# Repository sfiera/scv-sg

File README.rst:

Super Cassette Vision with Sega controllers
===========================================

.. image:: doc/pcb.png
   :alt: Adapter PCB
   :width: 400

This is an adapter board to connect early Sega controllers (SG-1000, SMS, Mega Drive) to an Epoch Super Cassette Vision console.

Schematic
---------

.. image:: doc/schematic.png
   :alt: KiCad Schematic

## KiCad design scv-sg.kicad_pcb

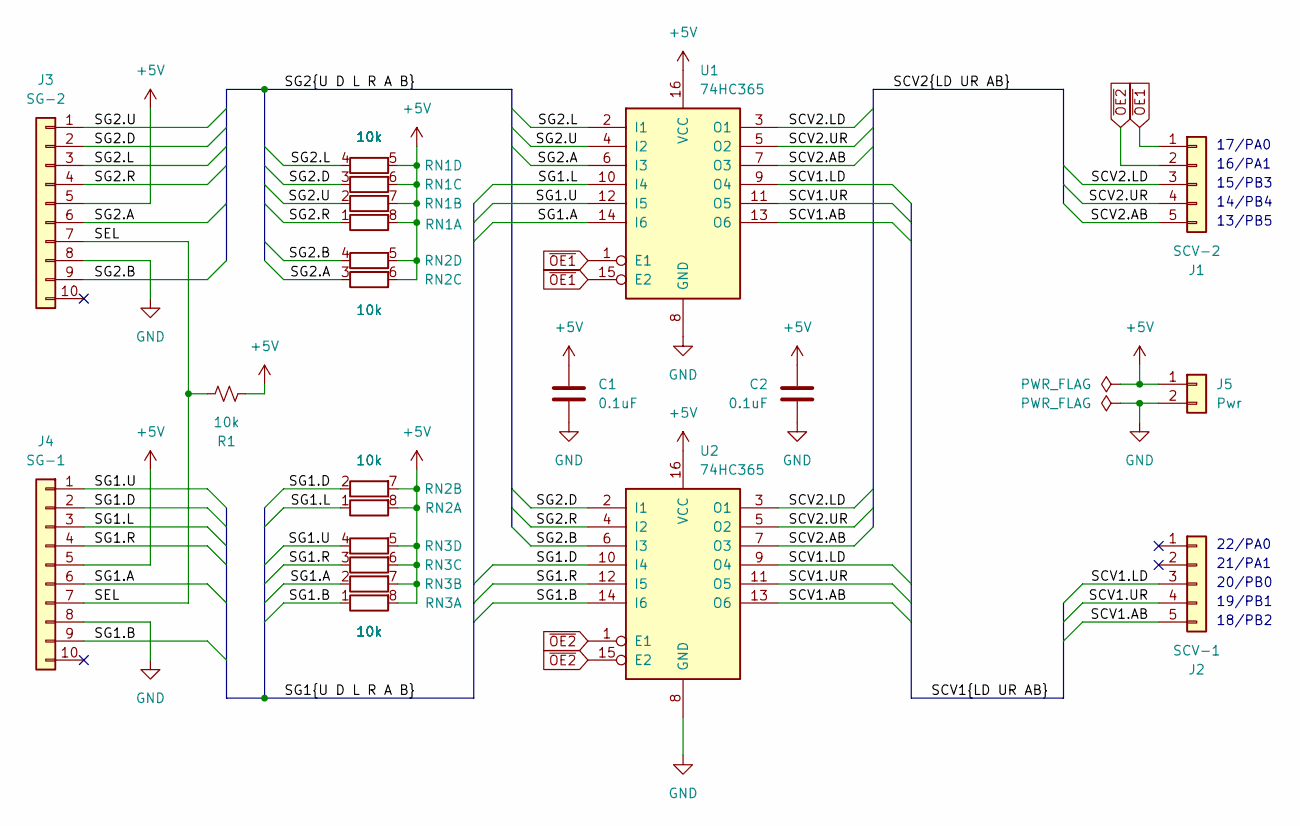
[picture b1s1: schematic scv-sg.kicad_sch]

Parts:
C1, C2: 0.1uF; C_0805_2012Metric
J1: SCV-2; PinHeader_1x05_P2.54mm_Vertical
J2: SCV-1; PinHeader_1x05_P2.54mm_Vertical
J3: SG-2; PinSocket_2x05_P2.54mm_Vertical
J4: SG-1; PinSocket_2x05_P2.54mm_Vertical
J5: Pwr; PinHeader_1x02_P2.54mm_Vertical
R1: 10k; R_0805_2012Metric
RN1, RN2, RN3: 10k; R_Array_Convex_4x0603
U1, U2: 74HC365; SOIC-16_3.9x9.9mm_P1.27mm

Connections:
+5V: C1.1, C2.1, J3.5, J4.5, J5.1, R1.1, RN1.5 (R4.2), RN1.6 (R3.2), RN1.7 (R2.2), RN1.8 (R1.2), RN2.5 (R4.2), RN2.6 (R3.2), RN2.7 (R2.2), RN2.8 (R1.2), RN3.5 (R4.2), RN3.6 (R3.2), RN3.7 (R2.2), RN3.8 (R1.2), U1.16 (VCC), U2.16 (VCC)
/SCV1.AB: J2.5, U1.13 (O6), U2.13 (O6)
/SCV1.LD: J2.3, U1.9 (O4), U2.9 (O4)
/SCV1.UR: J2.4, U1.11 (O5), U2.11 (O5)
/SCV2.AB: J1.5, U1.7 (O3), U2.7 (O3)
/SCV2.LD: J1.3, U1.3 (O1), U2.3 (O1)
/SCV2.UR: J1.4, U1.5 (O2), U2.5 (O2)
/SEL: J3.7, J4.7, R1.2
/SG1.A: J4.6, RN3.2 (R2.1), U1.14 (I6)
/SG1.B: J4.9, RN3.1 (R1.1), U2.14 (I6)
/SG1.D: J4.2, RN2.2 (R2.1), U2.10 (I4)
/SG1.L: J4.3, RN2.1 (R1.1), U1.10 (I4)
/SG1.R: J4.4, RN3.3 (R3.1), U2.12 (I5)
/SG1.U: J4.1, RN3.4 (R4.1), U1.12 (I5)
/SG2.A: J3.6, RN2.3 (R3.1), U1.6 (I3)
/SG2.B: J3.9, RN2.4 (R4.1), U2.6 (I3)
/SG2.D: J3.2, RN1.3 (R3.1), U2.2 (I1)
/SG2.L: J3.3, RN1.4 (R4.1), U1.2 (I1)
/SG2.R: J3.4, RN1.1 (R1.1), U2.4 (I2)
/SG2.U: J3.1, RN1.2 (R2.1), U1.4 (I2)
GND: C1.2, C2.2, J3.8, J4.8, J5.2, U1.8 (GND), U2.8 (GND)
~OE1: J1.1, U1.1 (E1), U1.15 (E2)
~OE2: J1.2, U2.1 (E1), U2.15 (E2)

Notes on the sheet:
16/PA1
15/PB3
14/PB4
21/PA1
13/PB5
17/PA0
18/PB2
19/PB1
22/PA0
20/PB0

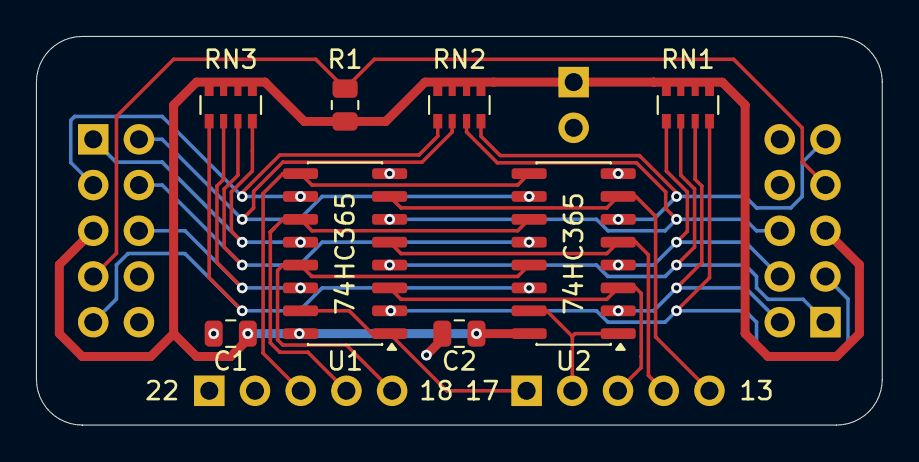
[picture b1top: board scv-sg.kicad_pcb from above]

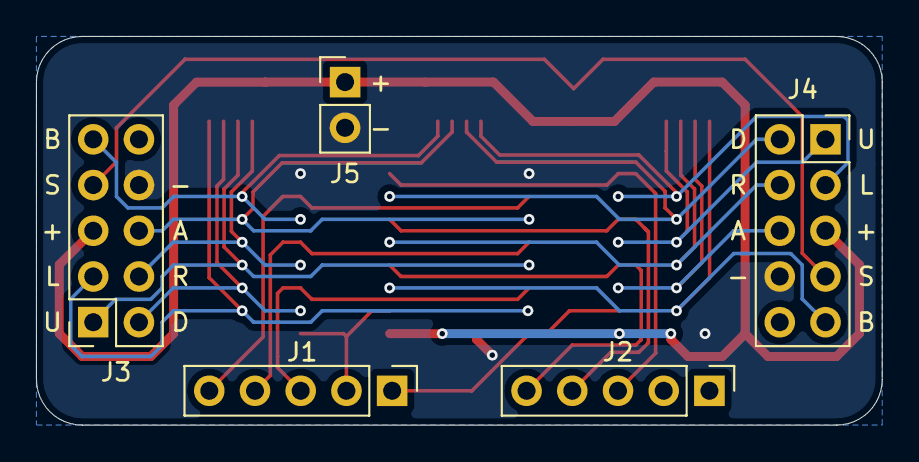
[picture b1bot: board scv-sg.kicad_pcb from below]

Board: 2 copper layers, 47.0 x 21.6 mm, 13 parts (5 on the bottom side), 23 nets.

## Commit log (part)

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2026-04-25 Update following testing
2026-04-25 Upgrade to KiCad 10
